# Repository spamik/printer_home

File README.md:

3D printer home
===============

Aluminium rack project for 3D printer(s) enclosure. In progress...

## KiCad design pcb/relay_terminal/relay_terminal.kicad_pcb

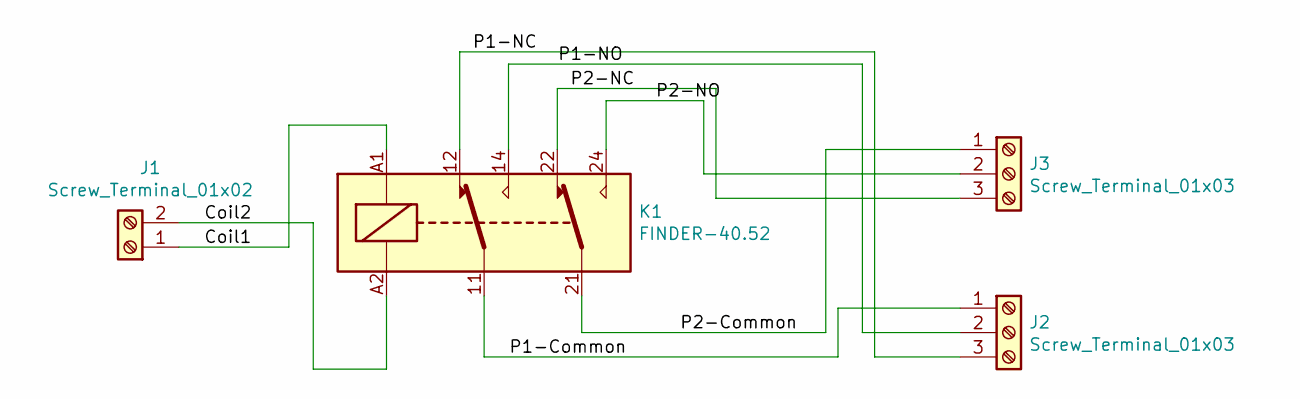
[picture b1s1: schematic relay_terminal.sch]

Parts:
J1: Screw_Terminal_01x02; TerminalBlock_RND_205-00001_1x02_P5.00mm_Horizontal
J2, J3: Screw_Terminal_01x03; TerminalBlock_RND_205-00002_1x03_P5.00mm_Horizontal
K1: FINDER-40.52; Relay_DPDT_Finder_40.52

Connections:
/Coil1: J1.1, K1.A1
/Coil2: J1.2, K1.A2
/P1-Common: J2.1, K1.11
/P1-NC: J2.3, K1.12
/P1-NO: J2.2, K1.14
/P2-Common: J3.1, K1.21
/P2-NC: J3.3, K1.22
/P2-NO: J3.2, K1.24

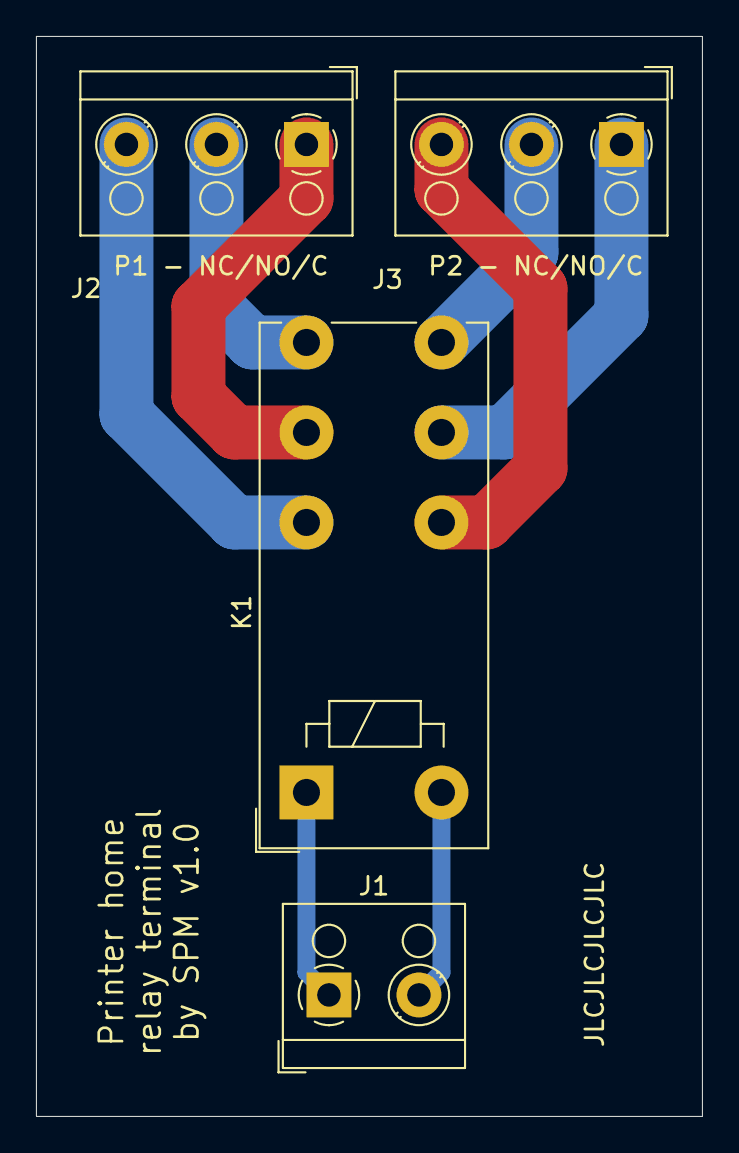
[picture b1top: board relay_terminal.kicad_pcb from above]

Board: 2 copper layers, 37.0 x 60.0 mm, 4 parts (0 on the bottom side), 8 nets.

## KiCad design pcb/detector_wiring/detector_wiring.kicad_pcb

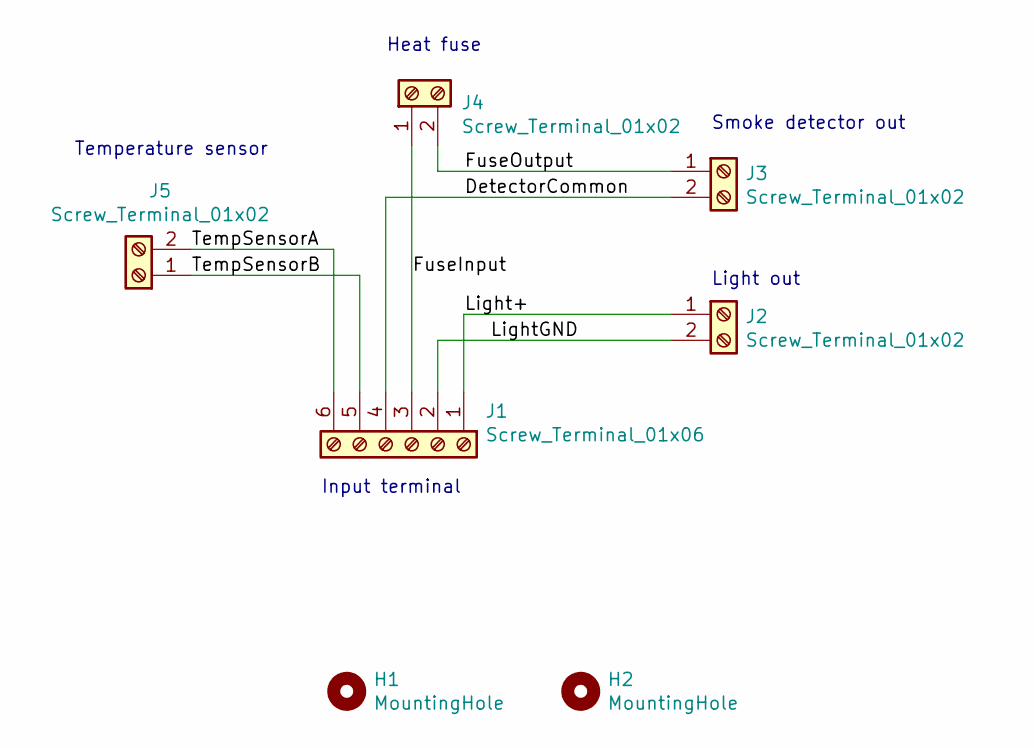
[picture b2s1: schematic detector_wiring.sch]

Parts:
H1, H2: MountingHole; MountingHole_2.5mm
J1: Screw_Terminal_01x06; TerminalBlock_RND_205-00005_1x06_P5.00mm_Horizontal
J2, J3, J4, J5: Screw_Terminal_01x02; TerminalBlock_RND_205-00001_1x02_P5.00mm_Horizontal

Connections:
/DetectorCommon: J1.4, J3.2
/FuseInput: J1.3, J4.1
/FuseOutput: J3.1, J4.2
/Light+: J1.1, J2.1
/LightGND: J1.2, J2.2
/TempSensorA: J1.6, J5.2
/TempSensorB: J1.5, J5.1

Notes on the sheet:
Light out
Input terminal
Smoke detector out
Heat fuse
Temperature sensor

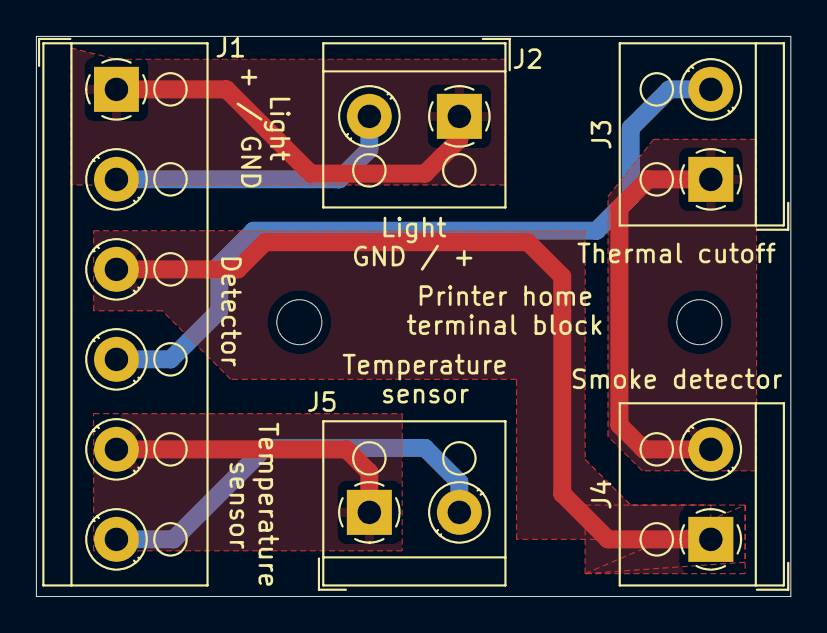
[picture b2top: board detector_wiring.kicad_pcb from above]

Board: 2 copper layers, 41.9 x 31.1 mm, 7 parts (0 on the bottom side), 7 nets.

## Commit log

2021-01-16 initial import
2021-01-16 Added readme file
2021-02-28 Added PCB design files for DIN relay board and terminal chamber board
2021-02-28 Added 3D models for switchboard socket panel
2021-03-28 Added cable pass and electro panel holder models
2022-12-04 Added cable pass for PTFE tube
2022-12-06 cable_pass_ptfe: fixed (forgotten mounting holes)
2022-12-06 Added model for fan cover on enclosure desks
2022-12-10 Updated cover desk drawings, added autocad exports
2022-12-10 Move drawing files
2022-12-10 Reorganization electric 3D model files
2022-12-10 Move fan filter model under electric
2022-12-10 Folder reorganization
